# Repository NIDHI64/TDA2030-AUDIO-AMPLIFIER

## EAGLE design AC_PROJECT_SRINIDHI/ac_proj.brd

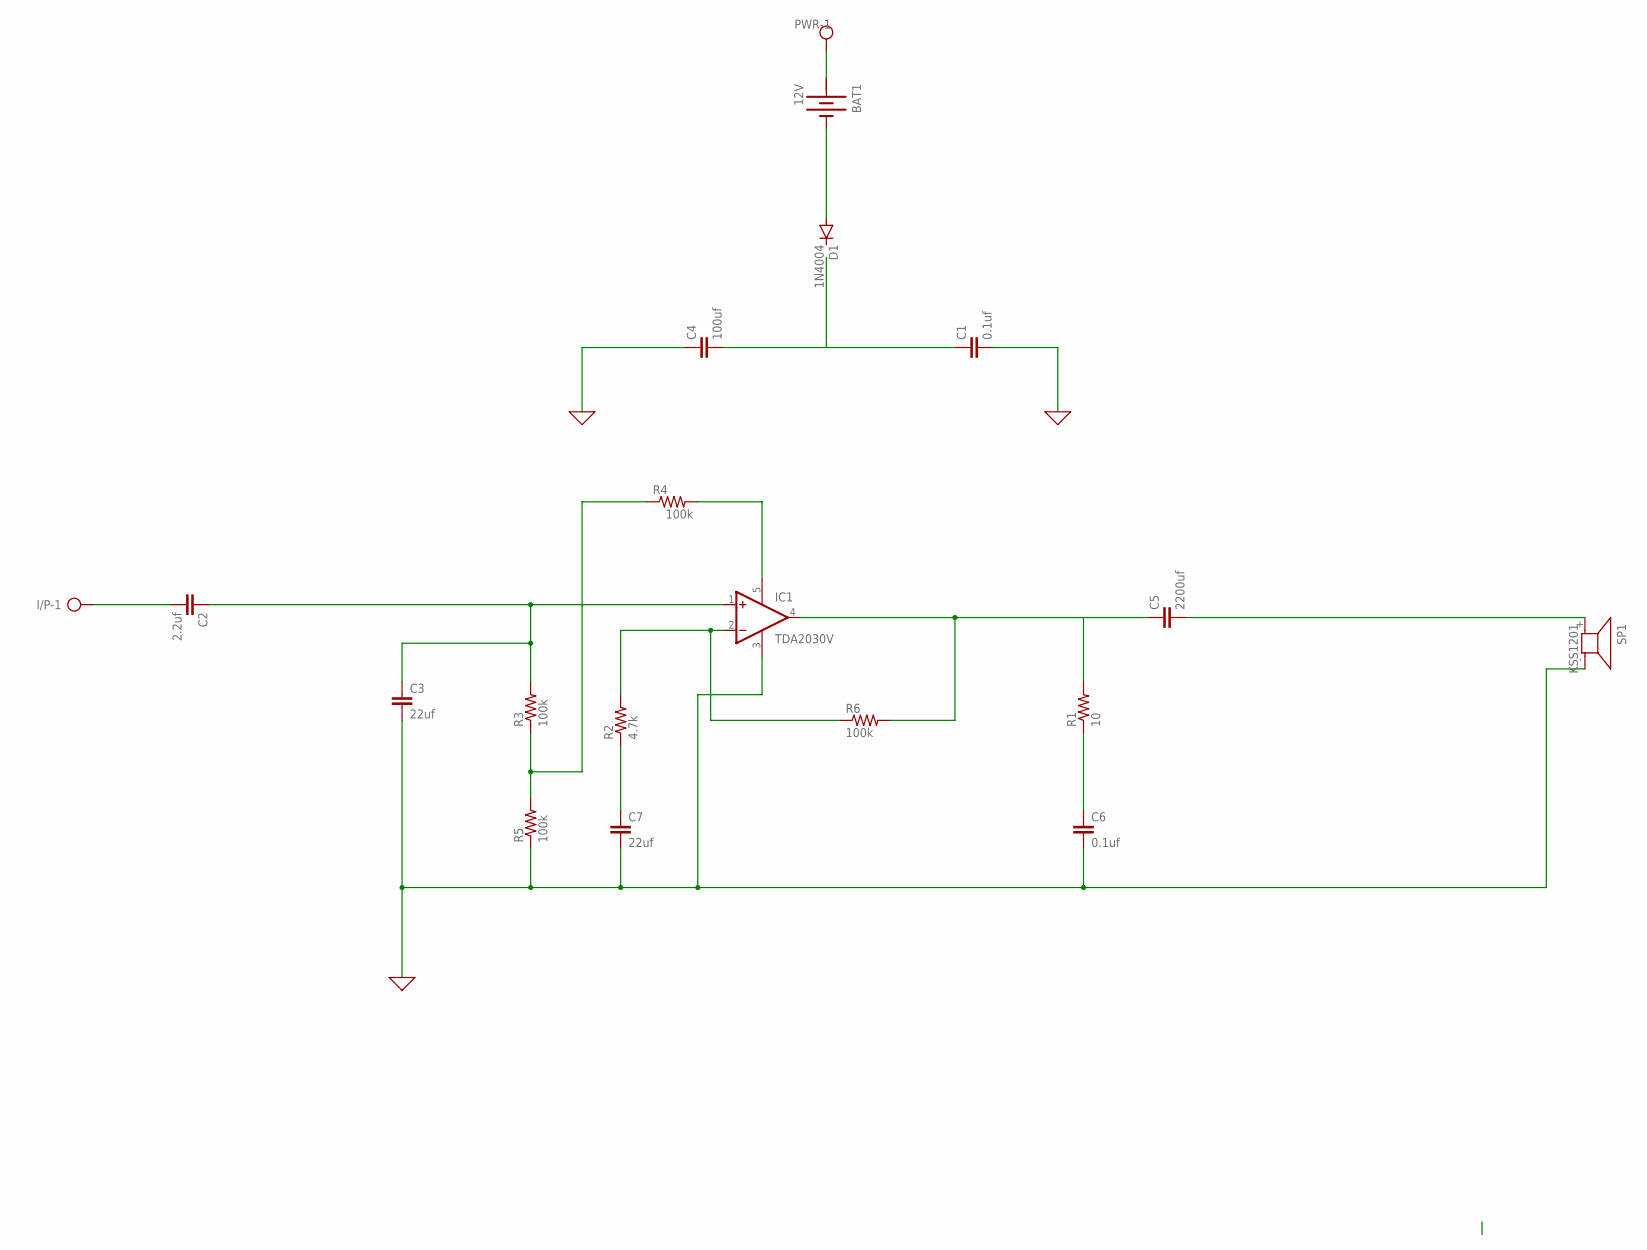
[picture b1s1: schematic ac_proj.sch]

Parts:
BAT1: 12V; BATTERY
C1, C6: 0.1uf; C5B3
C2: 2.2uf; C5B3
C3, C7: 22uf; C5B3
C4: 100uf; C5B3
C5: 2200uf; C5B3
D1: 1N4004; DO41-10
I/P: AK500/2-H
IC1: TDA2030V; CB360
PWR: AK500/2-H
R1: 10; 0411/15
R2: 4.7k; 0411/15
R3, R4, R5, R6: 100k; 0411/15
SP1: KSS1201

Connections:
0: C1.2, C3.2, C4.1, C6.2, C7.2, IC1.3 (GND), R5.1, SP1.- (2)
+: BAT1.+@1 (+)
unnamed: C2.1, C3.1, IC1.1 (+IN), R3.2
unnamed: R3.1, R4.1, R5.2
unnamed: C2.2, I/P.1
unnamed: C1.1, C4.2
unnamed: IC1.5 (V+), R4.2
unnamed: BAT1.-, D1.A
unnamed: BAT1.+, PWR.1
unnamed: IC1.2 (-IN), R2.2, R6.1
unnamed: C7.1, R2.1
unnamed: C5.1, IC1.4 (OUT), R1.2, R6.2
unnamed: C5.2, SP1.+ (1)
unnamed: C6.1, R1.1

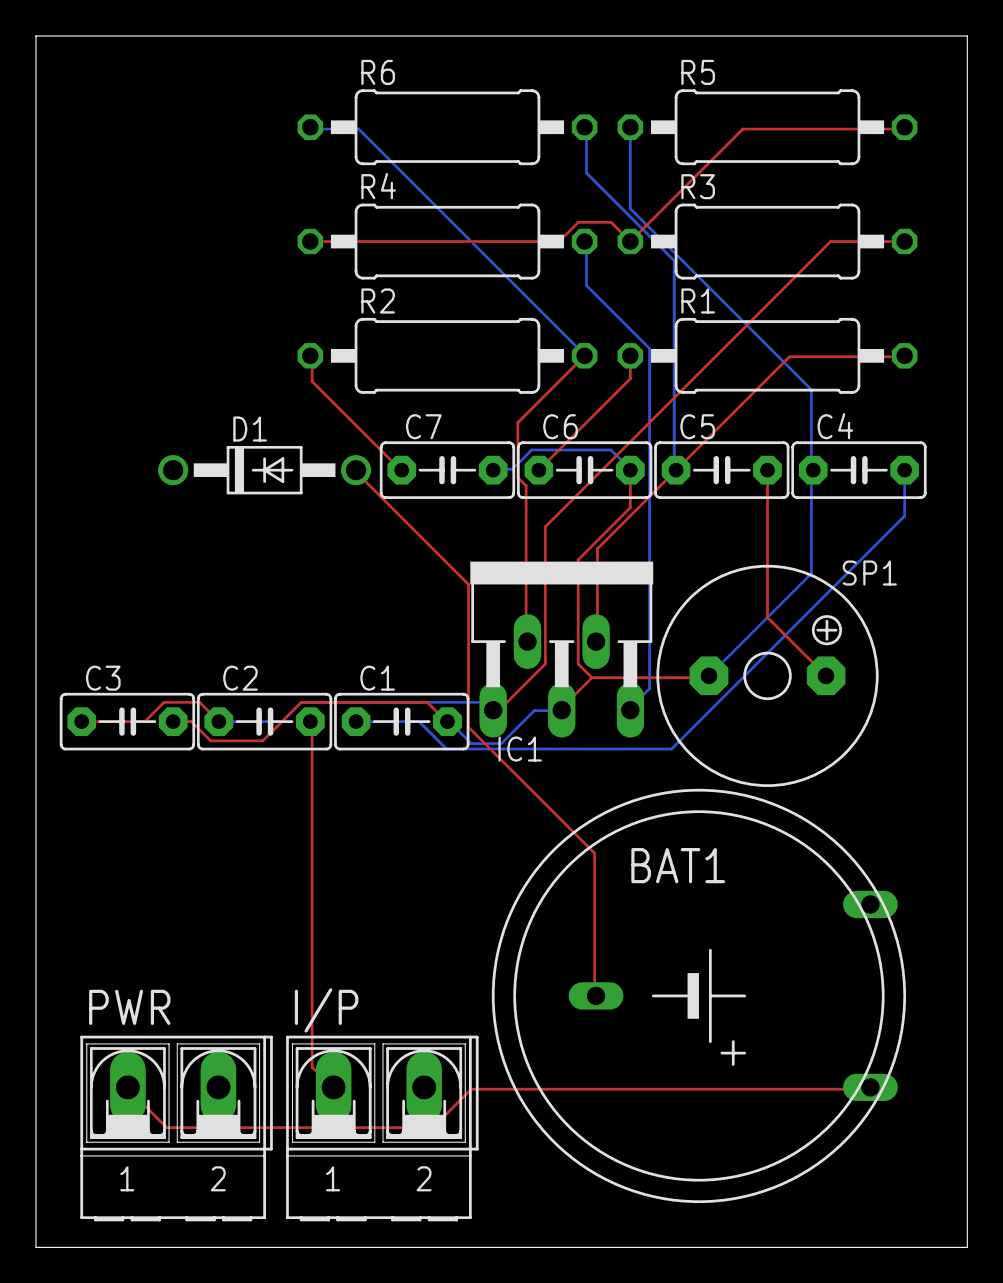
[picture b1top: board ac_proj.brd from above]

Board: 2 copper layers, 51.7 x 67.3 mm, 19 parts (0 on the bottom side), 13 nets.
